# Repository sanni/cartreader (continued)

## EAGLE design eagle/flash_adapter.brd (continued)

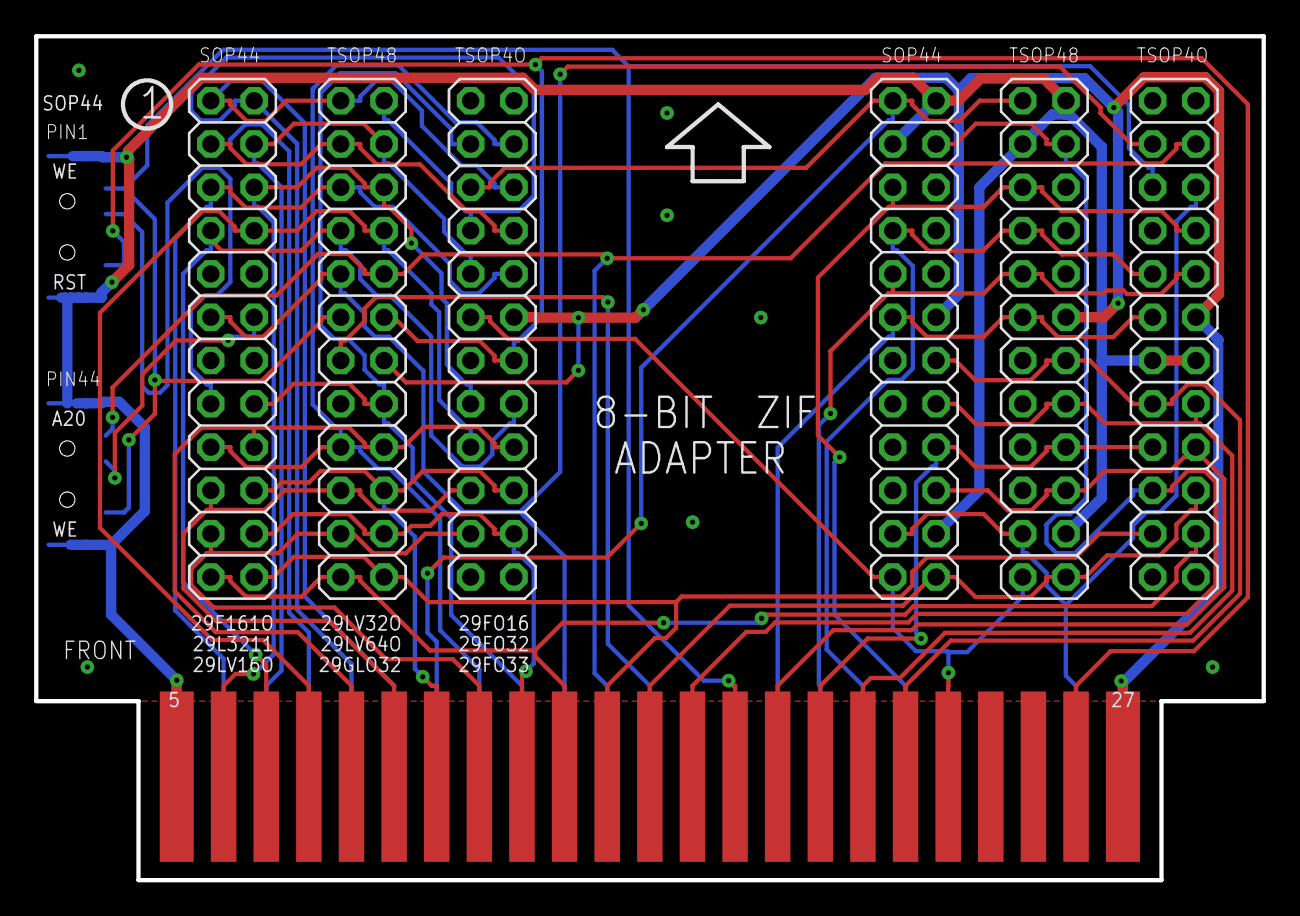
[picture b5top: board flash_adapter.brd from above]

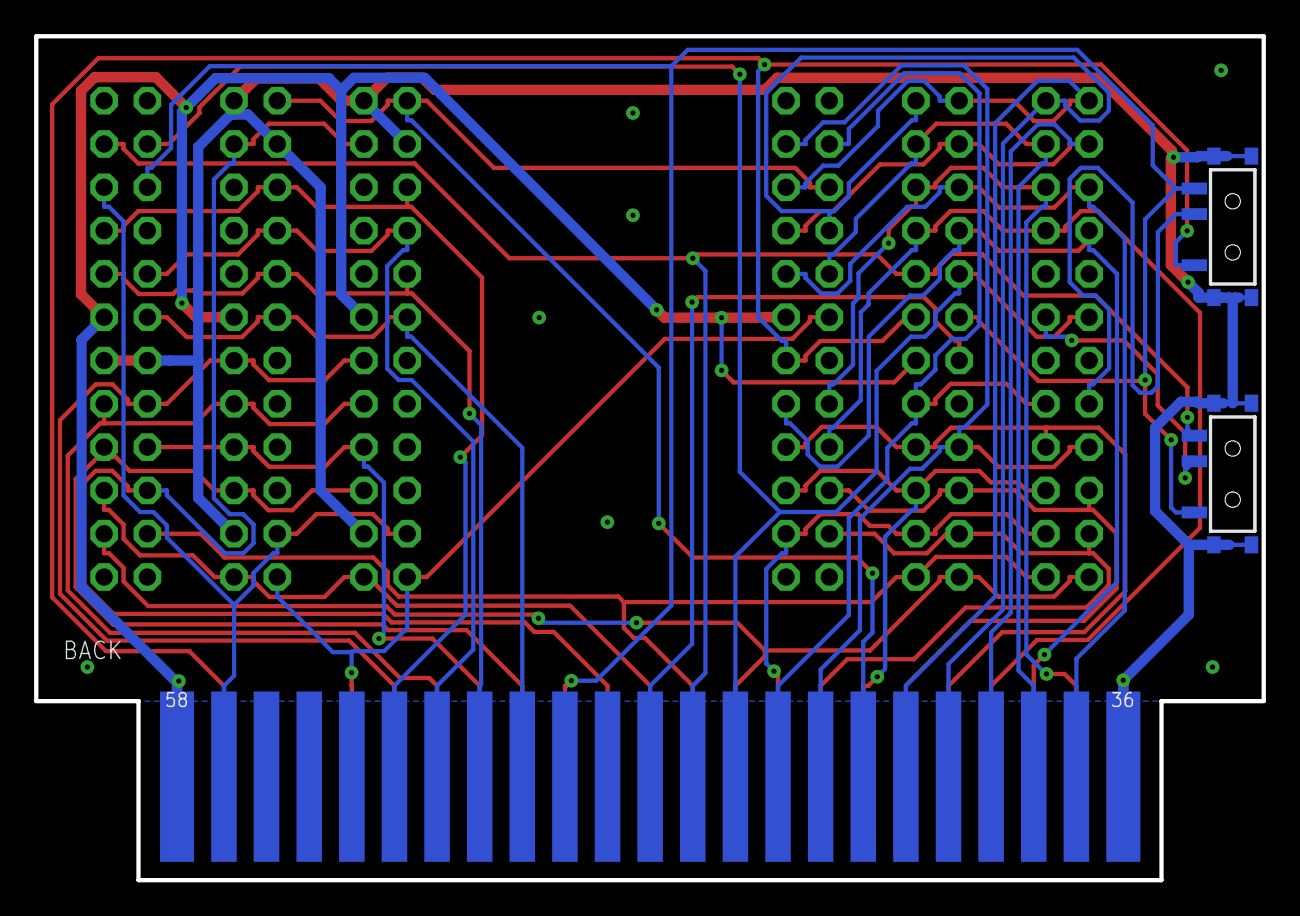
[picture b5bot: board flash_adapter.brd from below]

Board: 2 copper layers, 72.0 x 49.5 mm, 9 parts (2 on the bottom side), 39 nets.

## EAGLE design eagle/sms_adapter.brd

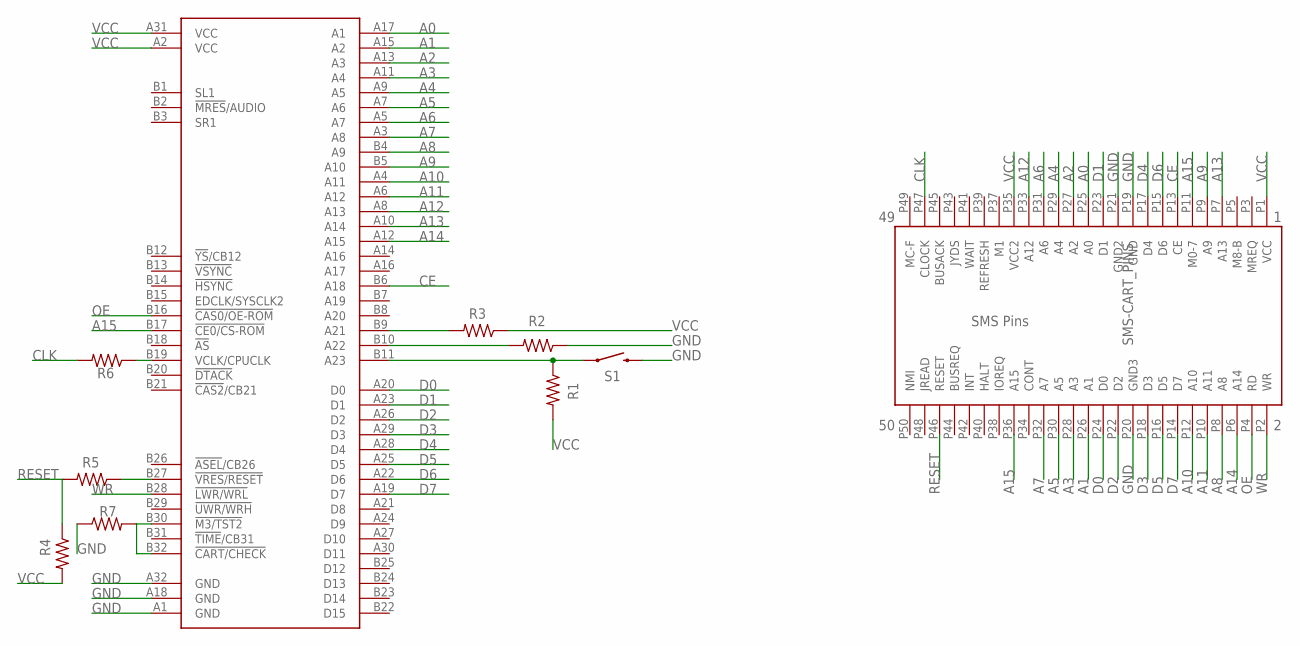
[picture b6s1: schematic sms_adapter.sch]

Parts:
CN3: MEGADRIVE-CART-CONNECTOR-ORDERED; MEGADRIVE-CART-CONNECTOR
R1: 56K; M1206
R2, R3, R4, R7: 0; M1206
R5, R6: NP; M1206
S1: MOMENTARY-SWITCH-SPST-SMD-5.2MM; TACTILE_SWITCH_SMD_5.2MM
U$1: SMS-CART_PINS; SMS_PINS

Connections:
A0: CN3.A17 (A1), U$1.P25 (A0)
A1: CN3.A15 (A2), U$1.P26 (A1)
A2: CN3.A13 (A3), U$1.P27 (A2)
A3: CN3.A11 (A4), U$1.P28 (A3)
A4: CN3.A9 (A5), U$1.P29 (A4)
A5: CN3.A7 (A6), U$1.P30 (A5)
A6: CN3.A5 (A7), U$1.P31 (A6)
A7: CN3.A3 (A8), U$1.P32 (A7)
A8: CN3.B4 (A9), U$1.P8 (A8)
A9: CN3.B5 (A10), U$1.P9 (A9)
A10: CN3.A4 (A11), U$1.P12 (A10)
A11: CN3.A6 (A12), U$1.P10 (A11)
A12: CN3.A8 (A13), U$1.P33 (A12)
A13: CN3.A10 (A14), U$1.P7 (A13)
A14: CN3.A12 (A15), U$1.P6 (A14)
A15: CN3.B17 (!CE0/CS-ROM), U$1.P11 (M0-7), U$1.P36 (A15)
CE: CN3.B6 (A18), U$1.P13 (CE)
CLK: R6.2, U$1.P47 (CLOCK)
D0: CN3.A20 (D0), U$1.P24 (D0)
D1: CN3.A23 (D1), U$1.P23 (D1)
D2: CN3.A26 (D2), U$1.P22 (D2)
D3: CN3.A29 (D3), U$1.P18 (D3)
D4: CN3.A28 (D4), U$1.P17 (D4)
D5: CN3.A25 (D5), U$1.P16 (D5)
D6: CN3.A22 (D6), U$1.P15 (D6)
D7: CN3.A19 (D7), U$1.P14 (D7)
GND: CN3.A1 (GND), CN3.A18 (GND), CN3.A32 (GND), R2.1, R7.1, S1.3 (2), U$1.P19 (GND), U$1.P20 (GND3), U$1.P21 (GND2)
unnamed: CN3.B11 (A23), R1.1, S1.1
unnamed: CN3.B10 (A22), R2.2
unnamed: CN3.B9 (A21), R3.2
unnamed: CN3.B19 (VCLK/CPUCLK), R6.1
unnamed: CN3.B30 (!M3/TST2), CN3.B32 (!CART/CHECK), R7.2
unnamed: CN3.B27 (!VRES/RESET), R5.1
OE: CN3.B16 (!CAS0/OE-ROM), U$1.P4 (RD)
RESET: R4.1, R5.2, U$1.P46 (RESET)
VCC: CN3.A2 (VCC), CN3.A31 (VCC), R1.2, R3.1, R4.2, U$1.P1 (VCC), U$1.P35 (VCC2)
WR: CN3.B28 (!LWR/WRL), U$1.P2 (WR)

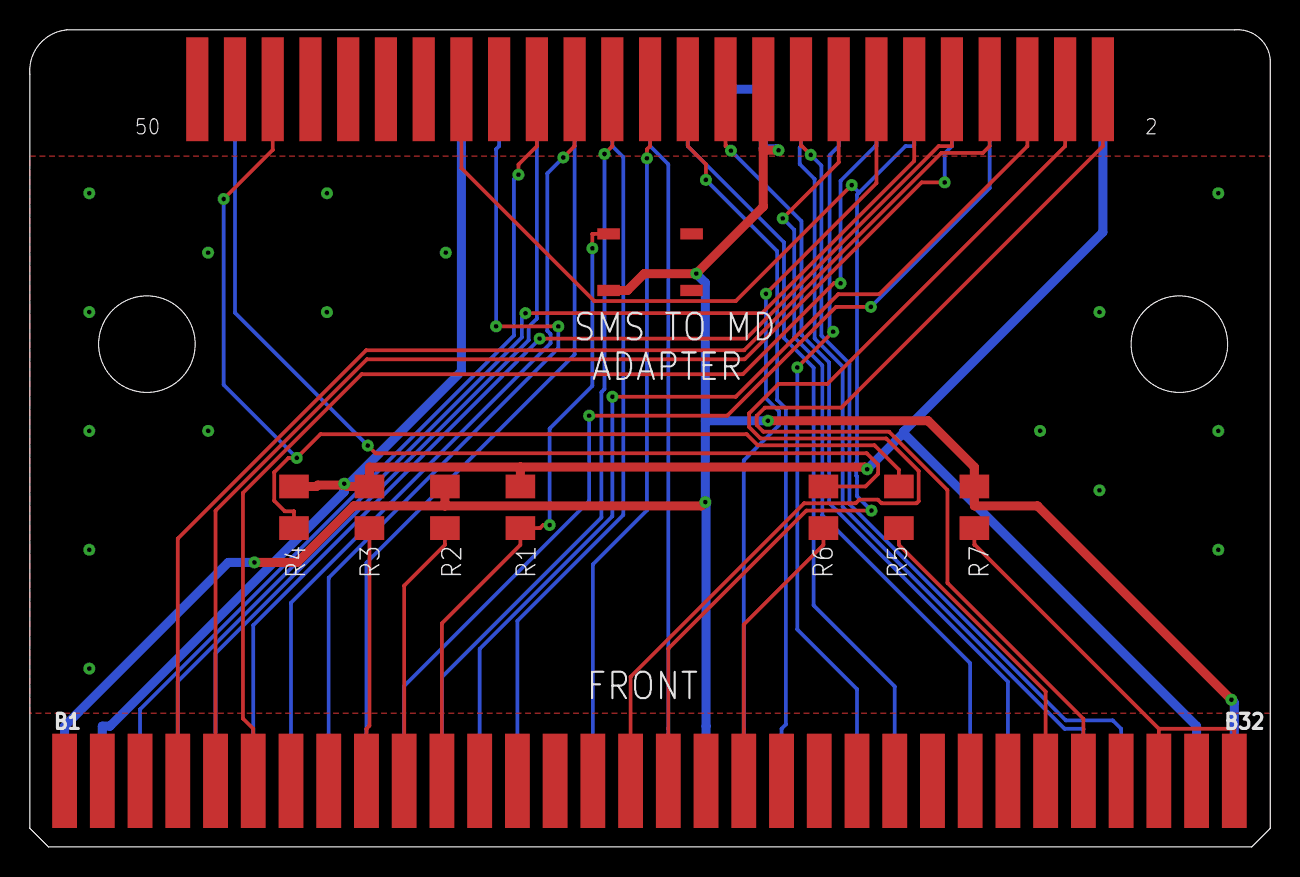
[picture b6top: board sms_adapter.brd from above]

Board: 2 copper layers, 83.5 x 55.0 mm, 10 parts (0 on the bottom side), 37 nets.

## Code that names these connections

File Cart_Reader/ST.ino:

/******************************************
  SUPER FAMICOM SUFAMI TURBO MODULE
******************************************/
#if (defined(ENABLE_ST) && defined(ENABLE_SNES))

/******************************************
  Menu
*****************************************/
// Sufami Turbo menu items
static const char stMenuItem1[] PROGMEM = "Read cart in Slot A";
static const char stMenuItem2[] PROGMEM = "Read cart in Slot B";
static const char* const menuOptionsST[] PROGMEM = { stMenuItem1, stMenuItem2, FSTRING_RESET };

void stMenu() {
  // Create ST menu with title and 3 options to choose from
  unsigned char mainMenu;
  convertPgm(menuOptionsST, 3);
  mainMenu = question_box(F("Sufami Turbo"), menuOptions, 3, 0);

  // Wait for user choice to come back from the question box menu
  switch (mainMenu) {
    // Read cart in ST slot A
    case 0:
      readSlot(0);
      break;

    // Read cart in ST slot B
    case 1:
      readSlot(1);
      break;

    // Reset
    case 2:
      resetArduino();
      break;
  }
}

/******************************************
   Setup
 *****************************************/
void setup_ST() {
  // Request 5V
  setVoltage(VOLTS_SET_5V);

  // Set cicrstPin(PG1) to Output
  DDRG |= (1 << 1);
  // Output a high signal until we're ready to start
  PORTG |= (1 << 1);
  // Set cichstPin(PG0) to Input
  DDRG &= ~(1 << 0);

  // Set Address Pins to Output
  //A0-A7
  DDRF = 0xFF;
  //A8-A15
  DDRK = 0xFF;
  //BA0-BA7
  DDRL = 0xFF;
  //PA0-PA7
  DDRA = 0xFF;

  // Set Control Pins to Output RST(PH0) CS(PH3) WR(PH5) RD(PH6)
  DDRH |= (1 << 0) | (1 << 3) | (1 << 5) | (1 << 6);
  // Switch RST(PH0) and WR(PH5) to HIGH
  PORTH |= (1 << 0) | (1 << 5);
  // Switch CS(PH3) and RD(PH6) to LOW
  PORTH &= ~((1 << 3) | (1 << 6));
  // Set Refresh(PE5) to Output
  DDRE |= (1 << 5);
  // Switch Refresh(PE5) to LOW (needed for SA-1)
  PORTE &= ~(1 << 5);
  // Set CPU Clock(PH1) to Output
  DDRH |= (1 << 1);
  // Set IRQ(PH4) to Input
  DDRH &= ~(1 << 4);
  // Set expand(PG5) to Input
  DDRG &= ~(1 << 5);
  // Set Data Pins (D0-D7) to Input
  DDRC = 0x00;
  // Unused pins
  // Set wram(PE4) to Output
  DDRE |= (1 << 4);
  // Set pawr(PJ1) to Output
  DDRJ |= (1 << 1);
  // Set pard(PJ0) to Output
  DDRJ |= (1 << 0);

  //Check if Sufami Turbo adapter is inserted
  if (!getHeader(0)) {
    display_Clear();
    println_Msg(F("Sufami Turbo adapter"));
    println_Msg(F("was not found."));
    display_Update();
    wait();
    resetArduino();
  }
}

/******************************************
  ROM Functions
******************************************/
// Verify if 'BANDAI' header is present in specified bank
bool getHeader(unsigned int bank) {
  byte snesHeader[16];
  PORTL = bank;

  // Read first bytes
  for (uint16_t c = 0, currByte = 0; c < 16; c++, currByte++) {
    PORTF = (currByte & 0xFF);
    PORTK = ((currByte >> 8) & 0xFF);
    NOP;
    NOP;
    NOP;
    NOP;
    NOP;
    NOP;
    snesHeader[c] = PINC;
  }

  // Format internal name
  buildRomName(romName, &snesHeader[0], 14);

  // Check if 'BANDAI' header is present
  if (strncmp(romName, "BANDAI SFC-ADX", 14) == 0)
    return (1);
  else
    return (0);
}

// Select the slot to use and detect cart size
void readSlot(bool cartSlot) {
  // Set control
  dataIn();
  controlIn_SNES();
  sd.chdir("/");
  display_Clear();

  if (!cartSlot) {           // Slot A was selected
    if (getHeader(32)) {     // Look for a cart in slot A
      if (getHeader(48))     // Look for mirrored data in slot A
        readRom_ST(32, 48);  // Dump 512KB cart
      else
        readRom_ST(32, 64);  // Dump 1MB cart
    }
    else {
      println_Msg(F("No cart detected in Slot A"));
      display_Update();
      wait();
    }
  }
  else {                      // Slot B was selected
    if (getHeader(64)) {      // Look for a cart in slot B
      if (getHeader(80))      // Look for mirrored data in slot B
        readRom_ST(64, 80);   // Dump 512KB cart
      else
        readRom_ST(64, 96);   // Dump 1MB cart
    }
    else {
      println_Msg(F("No cart detected in Slot B"));
      display_Update();
      wait();
    }
  }
}

// Read ST rom to SD card
void readRom_ST(unsigned int bankStart, unsigned int bankEnd) {
  // create a new folder to save rom file
  createFolderAndOpenFile("ST", "ROM", "SUFAMI_TURBO", "st");

  // Read specified banks
  readLoRomBanks(bankStart + 0x80, bankEnd + 0x80, &myFile);

  // Close file:
  myFile.close();

  // Compare dump CRC with db values
  compareCRC("st.txt", 0, 1, 0);

  println_Msg(FS(FSTRING_EMPTY));
  print_STR(press_button_STR, 1);
  display_Update();
  wait();
}
#endif

//******************************************
// End of File
//******************************************

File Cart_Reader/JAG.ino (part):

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// DATA D8-D15 - PORTK
// DATA D16-D23 - PORTL
// DATA D24-D31 - PORTC
// 74HC595 (ADDR) PINS - PORTE: ADDR (PE3-PJ0), SRCLR (PE4), SRCLK (PE5)
//                       PORTG: RCLK (PG5)
// EEPROM PINS - EEPDO (PA5), EEPSK (PA6), EEPCS (PA7), [EEPDI = DATA D0 (PF0)]
// CONTROL PINS - PORTH: OEH (PH3), OEL (PH4), CE (PH5), WE (PH6)

//******************************************
//  Defines
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byte jagSaveType = 0;  // Serial EEPROM

// SERIAL EEPROM 93CX6
// CONTROL: EEPCS (PA7), EEPSK (PA6), EEPDI (PF0) [DATA D0]
// SERIAL DATA OUTPUT: EEPDO (PA5)
#define EEP_CS_SET PORTA |= (1 << 7)
#define EEP_CS_CLEAR PORTA &= ~(1 << 7)
#define EEP_SK_SET PORTA |= (1 << 6)
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  // Request 5V
  setVoltage(VOLTS_SET_5V);

  // Set Address Pins to Output ADDR(PE3)(PJ0), SRCLR(PE4), SRCLK(PE5), RCLK(PG5)
  DDRE |= (1 << 3) | (1 << 4) | (1 << 5);
  DDRG |= (1 << 5);

  // Set Control Pins to Output OEH(PH3), OEL(PH4), CE(PH5), WE(PH6)
  DDRH |= (1 << 3) | (1 << 4) | (1 << 5) | (1 << 6);

  // Set EEPROM Control Pins to Output EEPSK(PA6), EEPCS(PA7)
  DDRA |= (1 << 6) | (1 << 7);

  // Set EEPROM Data to Input EEPDO(PA5)
  DDRA &= ~(1 << 5);

  // Set Data Pins (D0-D31) to Input
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  DDRL = 0x00;
  DDRC = 0x00;

  // Set Control Pins HIGH - OEH(PH3), OEL(PH4), CE(PH5), WE(PH6)
  PORTH |= (1 << 3) | (1 << 4) | (1 << 5) | (1 << 6);

  // Set 74HC595 (Address) Clear LOW - SRCLR (PE4)
  PORTE &= ~(1 << 4);  // Disable Address Shift Register

  EEPROM_readAnything(8, jagromSize);
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// SHIFT OUT
//******************************************************************************
// SHIFT OUT ADDRESS CODE
// SN74HC595 (ADDR) PINS - PORTE: ADDR (PJ3-PE3), SRCLR (PE4), SRCLK (PE5)
//                         PORTG: RCLK (PG5)
// DATA (SER/DS) PIN 14 = PE3 PJ0
// /OE (GND) PIN 13
// LATCH (RCLK/STCP) PIN 12 - LO/HI TO OUTPUT ADDRESS = PG5
// CLOCK (SRCLK/SHCP) PIN 11 - LO/HI TO READ ADDRESS  = PE5
// RESET (/SRCLR//MR) PIN 10  = PE4

#define SER_CLEAR PORTE &= ~(1 << 3);
#define SER_SET PORTE |= (1 << 3);
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  // Arduino running at 16Mhz -> one nop = 62.5ns
  __asm__("nop\n\t");

  // Setting CE(PH5) LOW
  PORTH &= ~(1 << 5);
  // Setting OEH3(PH3) + OEL(PH4) LOW
  PORTH &= ~(1 << 3) & ~(1 << 4);

  // Long delay here or there will be read errors
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  tempDataLO = (((PINK & 0xFF) << 8) | (PINF & 0xFF));  // D0-D15 [ROM U1]
  tempDataHI = (((PINC & 0xFF) << 8) | (PINL & 0xFF));  // D16-D31 [ROM U2]

  // Setting OEH(PH3) + OEL(PH4) HIGH
  PORTH |= (1 << 3) | (1 << 4);
  // Setting CE(PH5) HIGH
  PORTH |= (1 << 5);
  __asm__("nop\n\t"
          "nop\n\t"
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
//*****************************************************************************
// MICROCHIP EEPROM 93C56/66/76/86 CODE
// SERIAL DATA OUTPUT (DO):  PIN PA5
//
// ISSI 93C46-3P EEPROM ONLY USES WORD MODE
// EEPROM CODE IS WRITTEN IN WORD MODE (16bit)
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  for (int i = 0; i < 16; i++) {
    EEP_SK_SET;
    _delay_us(1);                         // minimum 250ns
    jagEepBit[i] = ((PINA & 0x20) >> 5);  // Read DO (PA5) - PINA with Mask 0x20
    EEP_SK_CLEAR;
    _delay_us(1);  // minimum 250ns
  }
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
  // CE or OE must be toggled with each subsequent status read or the
  // completion of a program or erase operation will not be evident.
  while (((PINL >> 6) & 0x1) == 0) {  // IO6 = PORTL PL6
    // Setting CE(PH5) HIGH
    PORTH |= (1 << 5);

    // Leave CE high for at least 60ns
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            "nop\n\t"
            "nop\n\t");

    // Setting CE(PH5) LOW
    PORTH &= ~(1 << 5);

    // Leave CE low for at least 50ns
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          "nop\n\t"
          "nop\n\t");

  // Setting CE(PH5) LOW
  PORTH &= ~(1 << 5);
  // Setting OEH(PH3) HIGH
  PORTH |= (1 << 3);
  // Setting OEL(PH4) LOW
  PORTH &= ~(1 << 4);

  __asm__("nop\n\t"
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  // Read
  byte tempByte = PINL;  // D16..D23

  // Setting CE(PH5) HIGH
  PORTH |= (1 << 5);
  // Setting OEL(PH4) HIGH
  PORTH |= (1 << 4);

  __asm__("nop\n\t"
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          "nop\n\t"
          "nop\n\t");

  // Setting CE(PH5) LOW
  PORTH &= ~(1 << 5);
  // Setting OEH(PH3) LOW
  PORTH &= ~(1 << 3);

  __asm__("nop\n\t"
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  // Read
  byte tempByte = PINF;  // D0..D7

  // Setting CE(PH5) HIGH
  PORTH |= (1 << 5);
  // Setting OEH(PH3) HIGH
  PORTH |= (1 << 3);

  __asm__("nop\n\t"
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          "nop\n\t"
          "nop\n\t");

  // Setting OEL(PH4) HIGH
  PORTH |= (1 << 4);
  // Setting CE(PH5) LOW
  PORTH &= ~(1 << 5);
  // Switch WE(PH6) LOW
  PORTH &= ~(1 << 6);
  delayMicroseconds(10);

  // Switch WE(PH6) HIGH
  PORTH |= (1 << 6);
  // Setting CE(PH5) HIGH
  PORTH |= (1 << 5);
  delayMicroseconds(10);
}
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            "nop\n\t"
            "nop\n\t");

    // Setting OEL(PH4) HIGH
    //    PORTH |= (1 << 4);
    // Setting CE(PH5) LOW
    PORTH &= ~(1 << 5);
    // Switch WE(PH6) LOW
    PORTH &= ~(1 << 6);
    __asm__("nop\n\t"
            "nop\n\t");  // Minimum 90ns

    // Switch WE(PH6) HIGH
    PORTH |= (1 << 6);
    // Setting CE(PH5) HIGH
    PORTH |= (1 << 5);

    __asm__("nop\n\t"
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
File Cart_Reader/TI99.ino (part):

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//                                        BOTTOM SIDE

// CONTROL PINS:
// RESET(PH0) - SNES RESET
// GRC(PH1)   - SNES CPUCLK [GROM CLOCK]
// /GS(PH3)   - SNES /CS    [GROM SELECT]
// DBIN(PH4)  - SNES /IRQ   [READ MEMORY/M(GROM DIRECTION)]
// /WE(PH5)   - SNES /WR
// /ROMS(PH6) - SNES /RD    [ROM SELECT]
// GR(PL0)    - SNES A16    [GROM READY]

// /GS = LOW FOR ADDR $9800-$9FFF
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  DDRL = 0xFE; // A16 to Input

  // Set Control Pins to Output
  //       RST(PH0)   GRC(PH1)   /GS(PH3)   DBIN(PH4)  /WE(PH5)  /ROMS(PH6)
  DDRH |=  (1 << 0) | (1 << 1) | (1 << 3) | (1 << 4) | (1 << 5) | (1 << 6);

  // Set TIME(PJ0) to Output (UNUSED)
  DDRJ |=  (1 << 0);

  // Set Pins (D0-D7) to Input
  DDRC = 0x00;

  // Setting Control Pins to HIGH
  //       RST(PH0)   GRC(PH1)   /GS(PH3)   DBIN(PH4)  /WE(PH5)  /ROMS(PH6)
  PORTH |= (1 << 0) | (1 << 1) | (1 << 3) | (1 << 4) | (1 << 5) | (1 << 6);

  // Set Unused Data Pins (PA0-PA7) to Output
  DDRA = 0xFF;

  // Set Unused PORTL Pins HIGH except GR(PL0)
  PORTL |= (1 << 1) | (1 << 2) | (1 << 3) | (1 << 4) | (1 << 5) | (1 << 6) | (1 << 7);

  // Set Unused Pins HIGH
  PORTA = 0xFF;
  PORTJ |= (1 << 0); // TIME(PJ0)

  // Set Reset LOW
  PORTH &= ~(1 << 0);
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  NOP;
  NOP;

  // Set /WE(PH5) to LOW
  PORTH &= ~(1 << 5); // /WE LOW
  NOP;
  NOP;
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  NOP;
  NOP;

  // Set /WE(PH5) to HIGH
  PORTH |= (1 << 5);
  NOP;
  NOP;
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
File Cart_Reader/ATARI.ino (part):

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  DDRL = 0xFF;

  // Set Control Pins to Output [UNUSED]
  //       ---(PH0)   ---(PH1)   ---(PH3)   ---(PH4)   ---(PH5)   ---(PH6)
  DDRH |= (1 << 0) | (1 << 1) | (1 << 3) | (1 << 4) | (1 << 5) | (1 << 6);

  // Set TIME(PJ0) to Output (UNUSED)
  DDRJ |= (1 << 0);

  // Set Pins (D0-D7) to Input
  DDRC = 0x00;

  // Setting Control Pins to HIGH [UNUSED]
  //       ---(PH0)   ---(PH1)   ---(PH3)   ---(PH4)   ---(PH5)   ---(PH6)
  PORTH |= (1 << 0) | (1 << 1) | (1 << 3) | (1 << 4) | (1 << 5) | (1 << 6);

  // Set Unused Data Pins (PA0-PA7) to Output
  DDRA = 0xFF;

  // Set Unused Pins HIGH
  PORTA = 0xFF;
  PORTL = 0xFF;       // A16-A23
  PORTJ |= (1 << 0);  // TIME(PJ0)

  checkStatus_ATARI();
  strcpy(romName, "ATARI");
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  int i = 0;
  // Check Button Status
#if defined(enable_OLED)
  buttonVal1 = (PIND & (1 << 7));  // PD7
#elif defined(enable_LCD)
  boolean buttonVal1 = (PING & (1 << 2));  //PG2
#endif

  if (buttonVal1 == LOW) {  // Button Pressed
    while (1) {             // Scroll Mapper List
#if defined(enable_OLED)
      buttonVal1 = (PIND & (1 << 7));  // PD7
#elif defined(enable_LCD)
      buttonVal1 = (PING & (1 << 2));      //PG2
#endif
      if (buttonVal1 == HIGH) {  // Button Released
        // Correct Overshoot
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#endif
  delay(2000);
#if defined(enable_OLED)
  buttonVal1 = (PIND & (1 << 7));  // PD7
#elif defined(enable_LCD)
  boolean buttonVal1 = (PING & (1 << 2));  //PG2
#endif
  if (buttonVal1 == LOW) {  // Button Held - Fast Cycle
    while (1) {             // Scroll Game List
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          Serial.println(atarigame);
#endif
#if defined(enable_OLED)
          buttonVal1 = (PIND & (1 << 7));  // PD7
#elif defined(enable_LCD)
          buttonVal1 = (PING & (1 << 2));  //PG2
#endif
          if (buttonVal1 == HIGH) {  // Button Released
            buttonreleased = 1;
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        }
      }
#if defined(enable_OLED)
      buttonVal1 = (PIND & (1 << 7));  // PD7
#elif defined(enable_LCD)
      buttonVal1 = (PING & (1 << 2));      //PG2
#endif
      if (buttonVal1 == HIGH)  // Button Released
        break;
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
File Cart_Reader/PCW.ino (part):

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//     +---------+

// CONTROL PINS:
// LE - (PH0) - PCW PIN 30 - SNES RST
// 1A - (PH3) - PCW PIN 27 - SNES /CS
// 1B - (PH4) - PCW PIN 26 - SNES /IRQ
// WE - (PH5) - PCW PIN 29 - SNES /WR
// OE - (PH6) - PCW PIN 28 - SNES /RD

// NOT CONNECTED:
// CLK(PH1) - N/C

// ADDRESS PINS:
// ADDR/DATA [AD0-AD7] - PORTC
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  DDRL = 0xFF;

  // Set Control Pins to Output
  //       LE(PH0)    --(PH1)    1A(PH3)    1B(PH4)    WE(PH5)    OE(PH6)
  DDRH |= (1 << 0) | (1 << 1) | (1 << 3) | (1 << 4) | (1 << 5) | (1 << 6);

  // Set TIME(PJ0) to Output (UNUSED)
  DDRJ |= (1 << 0);

  // Set Address/Data Pins AD0-AD7 (PC0-PC7) to Input
  MODE_READ;  // DDRC = 0

  // Setting Control Pins to HIGH
  //        LE(PH0)   ---(PH1)    1A(PH3)    1B(PH4)    WE(PH5)    OE(PH6)
  PORTH |= (1 << 0) | (1 << 1) | (1 << 3) | (1 << 4) | (1 << 5) | (1 << 6);

  // Set Unused Pins HIGH
  PORTJ |= (1 << 0);  // TIME(PJ0)

  strcpy(romName, "PCW");

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
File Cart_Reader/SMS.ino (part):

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    PORTL &= ~(1 << 1);
    DDRH &= ~((1 << 0) | (1 << 5));
    DDRL &= ~((1 << 1));
    // Set Control Pins to Output OE(PH6)
    DDRH |= (1 << 6);
    // WR(PL5) and RD(PL6)
    DDRL |= (1 << 5) | (1 << 6);
    // Setting OE(PH6) HIGH
    PORTH |= (1 << 6);
    // Setting WR(PL5) and RD(PL6) HIGH
    PORTL |= (1 << 5) | (1 << 6);
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
  // For Raphnet and Retron adapters
  else {
    // Set Control Pins to Output RST(PH0) WR(PH5) OE(PH6)
    DDRH |= (1 << 0) | (1 << 5) | (1 << 6);
    // CE(PL1)
    DDRL |= (1 << 1);
    // Setting RST(PH0) WR(PH5) OE(PH6) HIGH
    PORTH |= (1 << 0) | (1 << 5) | (1 << 6);
    // CE(PL1)
    PORTL |= (1 << 1);
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  PORTF = myAddress & 0xFF;
  PORTK = (myAddress >> 8) & 0xFF;
  if (!adapter_retrode) {
    // A15/M0-7(PH3) and OE(PH6) are connected
    PORTH = (PORTH & 0b11110111) | ((myAddress >> 12) & 0b00001000);
  }

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          "nop\n\t");

  if (adapter_retrode) {
    // Switch WR(PL5) and OE/CE(PH6) to LOW
    PORTL &= ~(1 << 5);
    PORTH &= ~(1 << 6);
  } else {
    // Switch CE(PL1) and WR(PH5) to LOW
    PORTL &= ~(1 << 1);
    PORTH &= ~(1 << 5);
  }
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          "nop\n\t");

  if (adapter_retrode) {
    // Switch WR(PL5) and OE/CE(PH6) to HIGH
    PORTH |= (1 << 6);
    PORTL |= (1 << 5);
  } else {
    // Switch CE(PL1) and WR(PH5) to HIGH
    PORTH |= (1 << 5);
    PORTL |= (1 << 1);
  }
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  PORTF = myAddress & 0xFF;
  PORTK = (myAddress >> 8) & 0xFF;
  if (!adapter_retrode) {
    // A15/M0-7(PH3) and OE(PH6) are connected
    PORTH = (PORTH & 0b11110111) | ((myAddress >> 12) & 0b00001000);
  }

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          "nop\n\t");

  if (adapter_retrode) {
    // Switch RD(PL6) and OE(PH6) to LOW
    PORTL &= ~(1 << 6);
    PORTH &= ~(1 << 6);
  } else {
    // Switch CE(PL1) and OE(PH6) to LOW
    PORTL &= ~(1 << 1);
    PORTH &= ~(1 << 6);
  }
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  byte tempByte = (adapter_retrode && system_gg) ? PINA : PINC;

  if (adapter_retrode) {
    // Switch RD(PL6) and OE(PH6) to HIGH
    PORTH |= (1 << 6);
    PORTL |= (1 << 6);
  } else {
    // Switch CE(PL1) and OE(PH6) to HIGH
    PORTH |= (1 << 6);
    PORTL |= (1 << 1);
  }
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
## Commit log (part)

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2024-04-22 remove some duplicate printing code and declare more global text strings
2024-04-24 replace cart select code with code used in NES, COLV, INTV
2024-04-27 replace 2600 cart selection code with code used in NES, COLV & INTV
2024-04-27 Update c64cart.txt
    Updated to work with C64.ino that fixes Issue #902
2024-04-28 replace C64 cart selection code with code used in NES, COLV & INTV
2024-04-28 fix ordering in 7800.txt
2024-04-28 fix formatting of newly added documentation
2024-04-29 add 5200 and arccart section to README.md
2024-05-01 replace FAIRCHILD, ODY2, MSX and VECTREX cart selection code with code used in NES, COLV & INTV. Define "Database not found" in OSCR.cpp
2024-05-01 remove duplicate CRC printing and calculation function
2024-05-01 remove duplicate code in printing CRC
2024-05-03 remove duplicate string literals
2024-05-03 fix signed/unsigned warning
2024-05-03 Add support for mapper 3E, 32K ROM 32K RAM Tigervision
2024-05-07 fix 2600 mapper selection for Serial
2024-05-07 Fixed (added) missing FS() macro on some FSTRING constants
    This was causing two symptoms/bugs:
    * OSCR_LOG.txt was being spammed with random data.
    * The size of OSCR_LOG.txt would get so big that copying the log would take a long time, possibly minutes. Oftentimes this caused the display to appear to hang after searching for the CRC (after "->"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
    If using the global log and a version of master since e61ac414d89556c941f0b8ca76e5d7d6684037f0 you should delete OSCR_LOG.txt from your SD card as it will likely be very large and continue to cause d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
2024-05-10 add serial printing to print instructions
2024-05-11 define "File doesn't exist" in OSCR.cpp/h
2024-05-12 reduce duplicate code by parameterise ROML/ROMH
2024-05-12 remove duplicate code for 2600 3E & 3F mapper
2024-05-12 use constant for "Saving to" instead declare the string several times
2024-05-20 remove duplicate code to open file for verfication
2024-05-20 remove duplicate code to write Flash Command
2024-05-24 support mapper > 255, implement mapper 446 submapper 0&1 - thanks to NewRisingSun for support, fix iNES2.0 mapper parsing of byte 8
2024-05-25 add option to clear display and remove duplicate code
2024-05-26 add common function to open create folder, print message and open file. Remove duplicate code
2024-05-28 define more commonly used string in OSCR and reuse them
2024-05-30 reuse code to write NES maker command
2024-05-30 reuse n64 flashrom Xplorer command sequence
2024-06-02 Add checks for unsafe configurations
    * Fixes #929
    * Updated `ci.yml` to define `GITHUB_CI`
    * Compilation will now error if VSELECT is enabled on hardware versions that don't support it (any version other than HW5).
    * HW4 and SERIAL might work but are untested. The error message for these versions reflects this.
    * Erroring when unsafe configurations are defined can be overridden by defining `ALLOW_UNSAFE_CONFIG` which will throw a warning instead.
    * This should only be done if trying to implement or test on a currently unsupported platform.
2024-06-03 reuse command sequence for GB
2024-06-10 Fix compilation errors when the FLASH core is enabled without FLASH16
    Commit References:
    * a32c6b3bfff066b04d81faea0e578b80cb4a3108 - Added ATTENTION_3_3V flash string but placed the definition inside a FLASH16 ifdef.
    * 4d000418a8f4e4a29297f83e30922100da7b21f5 - Added use of writeWord_Flash to FLASH8 without removing the FLASH16 ifdef around it.
2024-06-13 Add option to force ROM size for MD carts
2024-06-15 replace duplicate error string "Can't open file"
2024-06-16 define common string "Select file"
2024-06-26 SNES: Add 2x2MB flash to CFI (thx to MouseBiteLabs)
2024-06-27 Fix verifyFlash()
2024-06-29 reuse common string "ROM Size: "
2024-06-29 Disable SRAM when flashing 2x2MB repro
2024-06-30 Cleaning up debug stuff
2024-06-30 Always disable SRAM when flashing any hirom repros
2024-06-30 Fix reading Bahamut Lagoon English Translation SRAM (thx to Cowboyjunkie)
    https://github.com/sanni/cartreader/issues/917
2024-06-30 Alternate fix
2024-07-02 Fix color cycling when idle
2024-07-05 13.5 Fix SFM flash menu
    https://github.com/sanni/cartreader/issues/980
2024-07-07 Cherry-picking firmware changes only for Lynx support
    Updating header comments
    Better blocksize detection, cleanups
2024-07-07 Further optimize detection, combine loops
2024-07-08 GBA: Add basic support for F0088H0 flash
    No bank switching yet so ROM limited to 16MB.
    Uses flash commands found [here](https://github.com/lesserkuma/FlashGBX/blob/master/FlashGBX/config/fc_AGB_6600M0U0BE.txt)
2024-07-09 GBA: Fix Blankcheck function
2024-07-12 GBA: Add option to dump F0088H0 repro
2024-07-19 Flash: Add progress bar to read/verify/blankcheck flashrom
2024-07-24 add Chess to 2600. This is a variant of Video Chess
2024-07-29 SMS Updates
    1. SMS cart size detection algorithm is updated based on bank count instead of multiples of detected cart size from the header.
    2. SMS cart size detection is only invoked if the "TMR SEGA" header is parsed for non-JP carts.
    3. Manual selection of ROM size is now present in the SMS/GG menus to allow for manual override as detection algorithm does not work correctly for Cloud Master and Penguin Land US SMS carts.
    4. SG-1000 Operation menu now allows for reset instead of relying on a power cycle.
2024-07-31 Output clock signal during self test
2024-08-01 Atari 5200 Updates
    1. Added CRC database lookup for ROM dump validation and file renaming
    2. Added delays to improve successful ROM dumping. Especially helps with
    2-chip ROMs
    3. Fixed database mapper config for Star Trek (not a 2-chip ROM)
2024-08-04 Adds flash cartridge support to Atari Lynx firmware
2024-08-07 Add new options to SNES CFI repro menu
2024-08-11 Change N64 timings
    Seems to more reliable read SRAM with some delays removed.
2024-08-13 Support Flash repro A29040B
2024-08-15 Remove "Rotate to Change Press to Select" spam from log file
2024-08-16 Disable N64 controller test by default
2024-08-16 Fix compiler warnings/errors
2024-08-16 Remove more co-dependencies
2024-08-28 Fix/cleanup the VSELECT Module project files
    * Fixed the field name for the LCSC part number so the BOM exports with the part numbers.
    * Removed the test points from the schematic as they are no longer needed.
    * Added notes for setting the ILIM resistor to the schematic.
    * Added an image of the PCB and PDF of the schematic.
    Note: The PCB itself didn't change, so it is still Rev 3.
2024-08-28 Update NES.ino - fix mapper 80+82
    fix mapper 80+82
2024-09-11 Add writing MD FlashKit with S29GL064N
2024-09-12 Release CPS3 OSCR Adapter commit
2024-09-13 Add support for 39F040 to flash programmer
2024-09-13 Update lynx.txt
    Fix title names
2024-09-15 GB: Only trigger audio and not WR on flash cart with audio as WE, add 39SF cart without MBC
2024-09-20 Add 39SF020 and 39SF010 to flashrom programmer
2024-10-03 add 2600 games "Ente und der Wolf, Der", "Feuerwehr im Einsatz" & "Moderne Ritter, Der"
2024-11-05 docs: update README.md
    Github -> GitHub
2024-11-09 LEAP.ino : fixed dumping and typos
    LEAP.ino : fixed dumping and typos
2024-11-14 Update NES.ino : added mapper 268 submapper 0
    Update NES.ino : added mapper 268 submapper 0
2024-11-27 Fix `printInstructions()` overriding `dont_log` state
2024-12-07 add Berzerk and Space Duel to 7800
2024-12-15 Update NES.ino
    fix mapper 52
2024-12-21 Update NES.ino
    - RAM dump extension changed from .bin to .sav for direct use with emulators (see https://github.com/sanni/cartreader/discussions/1049)
    - regrouped scripts for MMC3-based mappers
    - regrouped scripts for CxROM-like mappers
    - regrouped scripts for BxROM-like mappers
    - added support for 268 submapper 1
2024-12-23 Update Cart_Reader.ino
    - Remove incomingByte global variable, mark all uses as local
    variables. This leads to a tiny (yet measurable) decrease in global
    variable use, and no change in sketch memory use. Of course, the
    variable now resides in the stack, but only while the functions using
    it exist, which isn't always.
2024-12-23 Update GB.ino
    - Move shared GB port initialization into its own function
2024-12-26 Update NES.ino
    Modified Mapper 226 to use pulsing M2 code (BMC Super 42-in-1, 76-in-1, et al.).
    Added Mapper 233 which requires power cycling the cart reader to switch between the two PRG chips (BMC 22-in-1/20-in-1 (42-in-1)).
2025-01-01 support "Bentley Bear's Crystal Quest" and "Bounty Bob Strikes Back!"
2025-01-01 Update nes.txt - sync'd with no-intro + sorted by release type
    Update nes.txt - sync'd with no-intro + sorted by release type instead of alphabetical: Licensed > Unlicensed > Pirate > Aftermarket. that will speed up things for the vast majority of users
2025-01-07 Fix offset address for mapper 24/26/78
2025-01-18 Update NES.ino
    - started mappers list cleanup
    - added mappers 12, 29, 115, 117, 120, 122, 125, 144, 182, 248, 532
2025-01-19 Update nes.txt
    sync'd with no-intro, reverted to default (alphabetical) order because it breaks game selection by name otherwise
2025-01-21 Update NES.ino
    Updated Mapper 45 to handle Dynavision 101 Games and 106 Games carts (4096K PRG). Added Mappers 237, 289, 319, and 332. Mappers 289 and 332 need pulsing M2 code to dump properly.
2025-01-22 Update NES.ino
    - mapper 268 typo fix
2025-01-24 Update NES.ino
    - added mapper 221, 288, 290
2025-01-26 Update NES.ino
    - added mappers 224, 396, 422, 534
    - added placeholders for 268 submappers 2-11 at fake numbers 995-999
2025-02-01 Update NES.ino
    - added mappers 272, 380, 519
2025-02-16 Update NES.ino
    Updated Mapper 178. Added Mapper 314. Mapper 314 needs pulsing M2 for register settings.
2025-02-26 Update VBOY.ino
    Add manual Rom size selection menu for unknown carts.
    Add 64KB Rom support.
    Add new serials to supported titles list.
2025-03-30 add DFSC Penult
2025-03-31 remove my HW define so automatic pull request may work
2025-04-18 add several Quelle Atari 2600 games
2025-04-25 Update Config.h - disabled A2600 that was ON by default
    disabled A2600 that was ON by default
2025-05-19 Adds support for M29F080 flash to PCE, tested
2025-05-22 Fix error when entering empty folder
2025-05-31 Remove unnecessary logs
2025-06-02 Add config tool for portable release
    This replaces that three *.bat files that are currently in the portable release.
2025-06-02 Remove compiled exe
2025-06-02 Start Arduino IDE with the Cart_Reader sketch already selected
2025-06-03 Fix script not closing if there is no error.
2025-06-13 Update NES.ino - added mapper 312
    added mapper 312 for Kaiser's Highway Star (untested)
2025-06-19 Update monthly_release.yml - Add 7zip archive
2025-06-19 Prevent arduino-cli from writing to \AppData\Local
2025-06-19 Fix avrdude timeout on old PC
2025-07-08 Update SNES.ino - Fix crashing menu when enabling Clock Calibration
2025-07-29 Re-structure GB repro menu & fix dumping GB ROM with no name in header
    MBC1 option probably not working yet
2025-08-07 Update NES.ino - fix mapper 380
    mapper 380 needs M2 pulse, tested working
2025-08-14 Use F() in MD.ino CFI code.
2025-08-18 Identify SRAM chip when flashing Genesis CFI.
    In a board with 1 flash chip and SRAM, the SRAM is always enabled so attempting
    to detect it as CFI will fail.
    This commit adds some simple code that attempts to modify address 0x0 of the
    chip to detect if the chip is ROM or SRAM. If the value changes upon writing to
    it, it will assume it's SRAM and ignore it when flashing.
2025-08-18 N64: fix default cartsize for unknown cart
2025-08-23 Bump version to V15.2 after bi-monthly release
2025-09-05 Add support for Genesis 29F800 under CFI.
    The 29F800 supports CFI commands as is except for the ID command, so this adds
    custom code to identify it.
    Rewrote the identifyCFI function a bit to make it more readable.
2025-09-07 Sort GBA database by cart ID and fix nulled out cart ID
2025-09-10 Update NES.ino - fix for Babel no Tou
    fix for Babel no Tou
2025-09-18 Update SMS.ino
    Comments added
2025-10-01 Bump version to V15.3 after bi-monthly release
2025-11-11 Support VSELECT on HW3
2025-12-05 Fix compile when MD/SNES are disabled
2025-12-07 add Telegames version of Bump'n'Jump
2025-12-19 NES: Fix some CRC32s
2025-12-20 Update driver URL
2025-12-20 Update AVR-GCC and Arduino CLI versions in workflow
2025-12-21 Update steps in bi-monthly release workflow
2025-12-23 Fix SD read in CRC calculation
2025-12-25 Make settings displaying optional when calling setup_7800()
2026-01-02 Redo gba database
2026-01-11 Add cleaning status dropdown to bug issue template
    Added a dropdown for cartridge pin cleaning status in bug template.
2026-03-07 [NES] Fixing incorrect control register for MMC1 CHR
    [NES] Fixing incorrect control register for MMC1 CHR, notably for SHROM and SEROM (Tetris, Dr. Mario, Boulder Dash, Anticipation and some more)
